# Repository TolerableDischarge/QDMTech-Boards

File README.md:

# QDMTech-Boards
A repo of all the boards designed by QuantumDarkMatter Tech.
v0.1 is very bad since I was learning as I was going for my Uni Project. There's a first time for everything I guess.
IMPORTANT: Right now the only thing under MIT license is the ZMK firmware files, the rest is a little murky. v0.2 will be MIT compatible.

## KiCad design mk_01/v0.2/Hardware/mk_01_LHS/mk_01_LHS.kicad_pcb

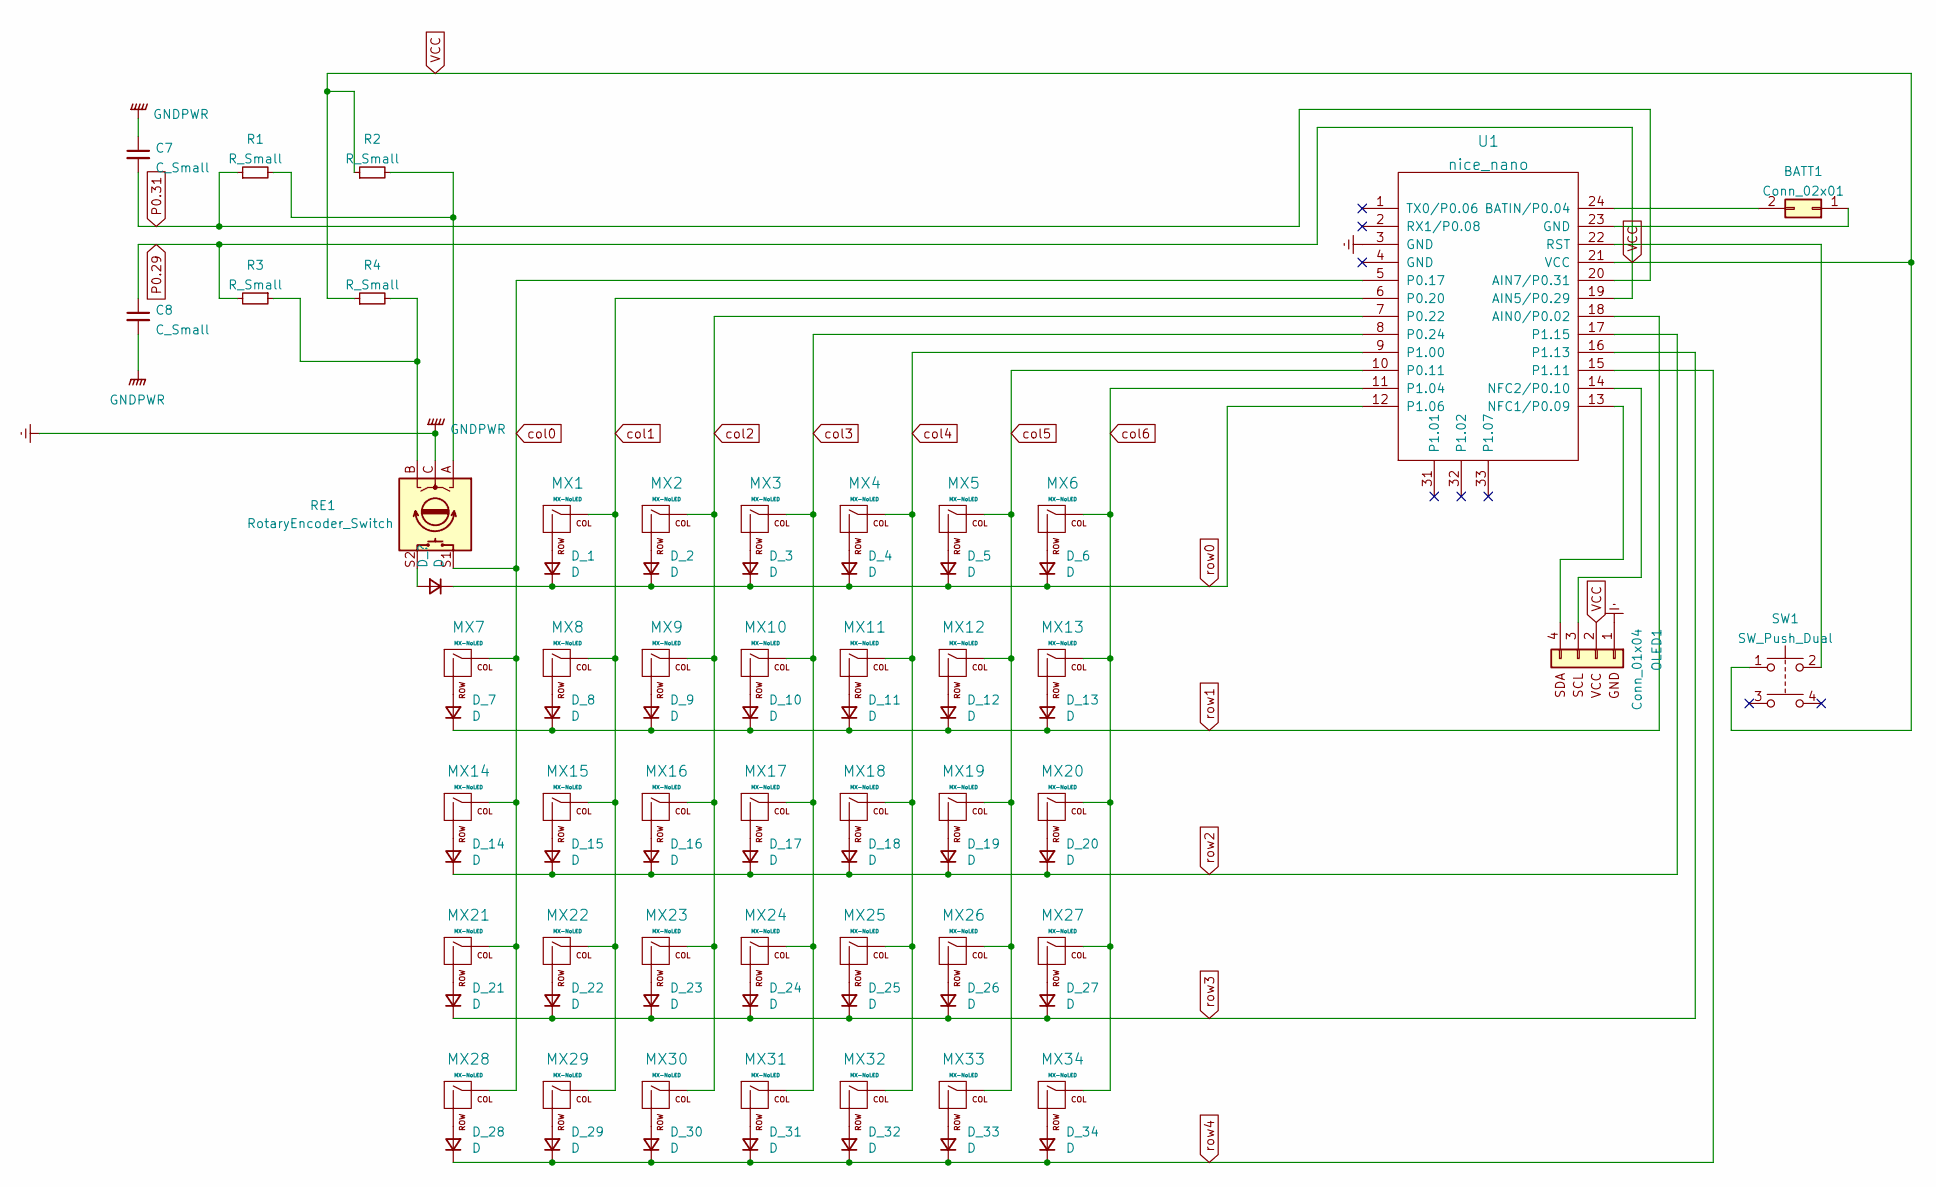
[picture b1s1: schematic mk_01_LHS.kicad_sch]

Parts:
BATT1: Conn_02x01; C_Rect_L41.5mm_W20.0mm_P37.50mm_MKS4
C7, C8: C_Small; C_0805_2012Metric_Pad1.18x1.45mm_HandSolder
D_1, D_2, D_3, D_4, D_5, D_6, D_7, D_8, D_9, D_10, D_11, D_12, D_13, D_14, D_15, D_16, D_17, D_18, D_19, D_20, D_21, D_22, D_23, D_24, D_25, D_26, D_27, D_28, D_29, D_30, D_31, D_32, D_33, D_34: D; D_SOD-123
MX1, MX2, MX3, MX4, MX5, MX6, MX7, MX8, MX9, MX10, MX11, MX12, MX13, MX14, MX15, MX16, MX17, MX18, MX19, MX20, MX21, MX22, MX23, MX24, MX25, MX26, MX27, MX28, MX29, MX30, MX31, MX32, MX33, MX34: MX-NoLED; MXOnly-1U-Hotswap-NoLED
OLED1: Conn_01x04; OLED_4Pin
R1, R2, R3, R4: R_Small; R_0805_2012Metric_Pad1.20x1.40mm_HandSolder
RE1: RotaryEncoder_Switch; RotaryEncoder_Alps_EC11E-Switch_Vertical_H20mm
SW1: SW_Push_Dual; SW_PUSH_6mm_H5mm
U1: nice_nano

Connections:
Earth: C7.1, C8.2, OLED1.1, RE1.C, U1.3 (GND), U1.4 (GND)
unnamed: BATT1.1, U1.23 (GND)
unnamed: BATT1.2, U1.24 (BATIN/P0.04)
unnamed: D_1.2 (A), MX1.2 (ROW)
unnamed: D_2.2 (A), MX2.2 (ROW)
unnamed: D_3.2 (A), MX3.2 (ROW)
unnamed: D_4.2 (A), MX4.2 (ROW)
unnamed: D_5.2 (A), MX5.2 (ROW)
unnamed: D_6.2 (A), MX6.2 (ROW)
unnamed: D_7.2 (A), MX7.2 (ROW)
unnamed: D_8.2 (A), MX8.2 (ROW)
unnamed: D_9.2 (A), MX9.2 (ROW)
unnamed: D_10.2 (A), MX10.2 (ROW)
unnamed: D_11.2 (A), MX11.2 (ROW)
unnamed: D_12.2 (A), MX12.2 (ROW)
unnamed: D_13.2 (A), MX13.2 (ROW)
unnamed: D_14.2 (A), MX14.2 (ROW)
unnamed: D_15.2 (A), MX15.2 (ROW)
unnamed: D_16.2 (A), MX16.2 (ROW)
unnamed: D_17.2 (A), MX17.2 (ROW)
unnamed: D_18.2 (A), MX18.2 (ROW)
unnamed: D_19.2 (A), MX19.2 (ROW)
unnamed: D_20.2 (A), MX20.2 (ROW)
unnamed: D_21.2 (A), MX21.2 (ROW)
unnamed: D_22.2 (A), MX22.2 (ROW)
unnamed: D_23.2 (A), MX23.2 (ROW)
unnamed: D_24.2 (A), MX24.2 (ROW)
unnamed: D_25.2 (A), MX25.2 (ROW)
unnamed: D_26.2 (A), MX26.2 (ROW)
unnamed: D_27.2 (A), MX27.2 (ROW)
unnamed: D_28.2 (A), MX28.2 (ROW)
unnamed: D_29.2 (A), MX29.2 (ROW)
unnamed: D_30.2 (A), MX30.2 (ROW)
unnamed: D_31.2 (A), MX31.2 (ROW)
unnamed: D_32.2 (A), MX32.2 (ROW)
unnamed: D_33.2 (A), MX33.2 (ROW)
unnamed: D_34.2 (A), MX34.2 (ROW)
unnamed: OLED1.3, U1.14 (NFC2/P0.10)
unnamed: OLED1.4, U1.13 (NFC1/P0.09)
unnamed: R1.2, R2.2, RE1.A
unnamed: R3.1, R4.2, RE1.B
unnamed 41: RE1.S2; also elsewhere on the board
unnamed: SW1.2, U1.22 (RST)
P0.31: C7.2, R1.1, U1.20 (AIN7/P0.31)
col0: MX7.1 (COL), MX14.1 (COL), MX21.1 (COL), MX28.1 (COL), RE1.S1, U1.5 (P0.17)
col1: MX1.1 (COL), MX8.1 (COL), MX15.1 (COL), MX22.1 (COL), MX29.1 (COL), U1.6 (P0.20)
col2: MX2.1 (COL), MX9.1 (COL), MX16.1 (COL), MX23.1 (COL), MX30.1 (COL), U1.7 (P0.22)
col3: MX3.1 (COL), MX10.1 (COL), MX17.1 (COL), MX24.1 (COL), MX31.1 (COL), U1.8 (P0.24)
col4: MX4.1 (COL), MX11.1 (COL), MX18.1 (COL), MX25.1 (COL), MX32.1 (COL), U1.9 (P1.00)
col5: MX5.1 (COL), MX12.1 (COL), MX19.1 (COL), MX26.1 (COL), MX33.1 (COL), U1.10 (P0.11)
col6: MX6.1 (COL), MX13.1 (COL), MX20.1 (COL), MX27.1 (COL), MX34.1 (COL), U1.11 (P1.04)
row0: D_1.1 (K), D_2.1 (K), D_3.1 (K), D_4.1 (K), D_5.1 (K), D_6.1 (K), U1.12 (P1.06); also elsewhere on the board
row1: D_7.1 (K), D_8.1 (K), D_9.1 (K), D_10.1 (K), D_11.1 (K), D_12.1 (K), D_13.1 (K), U1.18 (AIN0/P0.02)
row2: D_14.1 (K), D_15.1 (K), D_16.1 (K), D_17.1 (K), D_18.1 (K), D_19.1 (K), D_20.1 (K), U1.17 (P1.15)
row3: D_21.1 (K), D_22.1 (K), D_23.1 (K), D_24.1 (K), D_25.1 (K), D_26.1 (K), D_27.1 (K), U1.16 (P1.13)
row4: D_28.1 (K), D_29.1 (K), D_30.1 (K), D_31.1 (K), D_32.1 (K), D_33.1 (K), D_34.1 (K), U1.15 (P1.11)

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
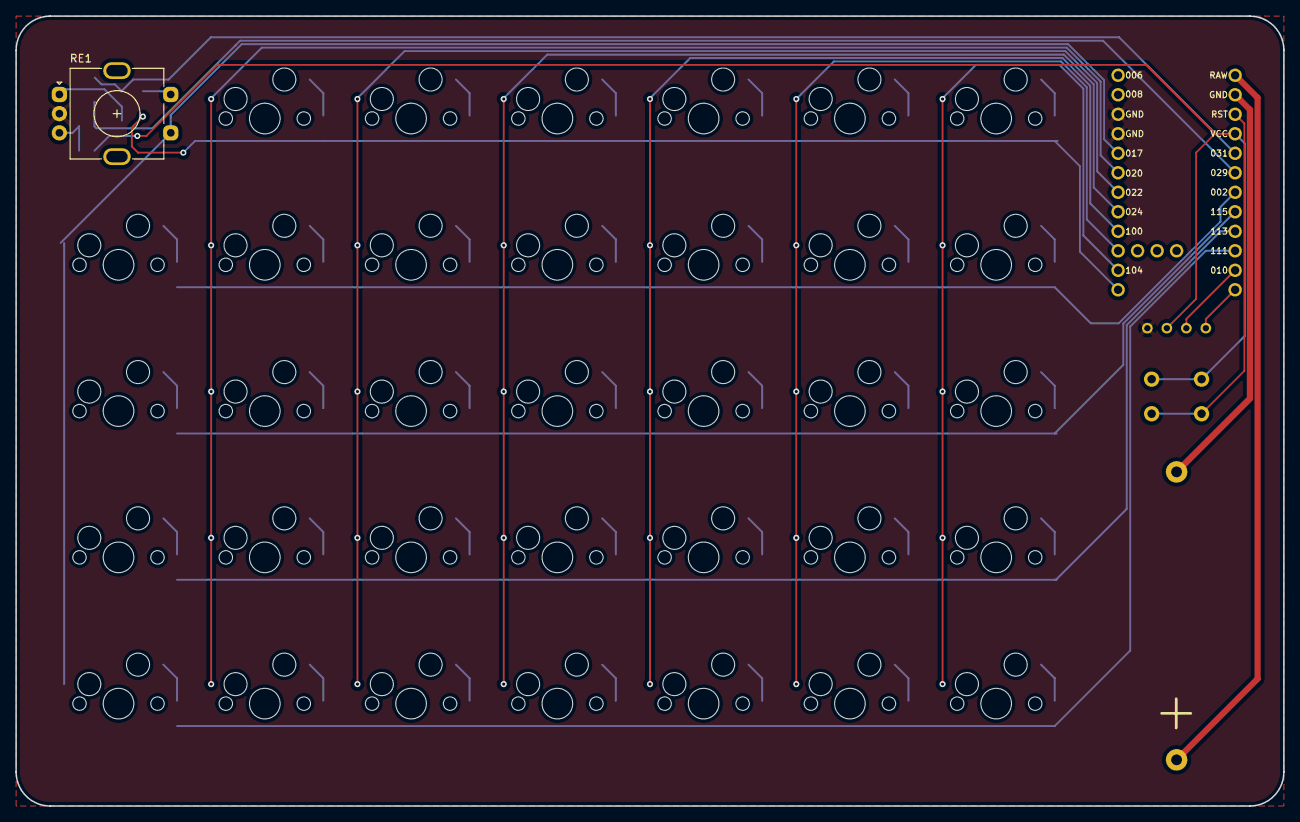
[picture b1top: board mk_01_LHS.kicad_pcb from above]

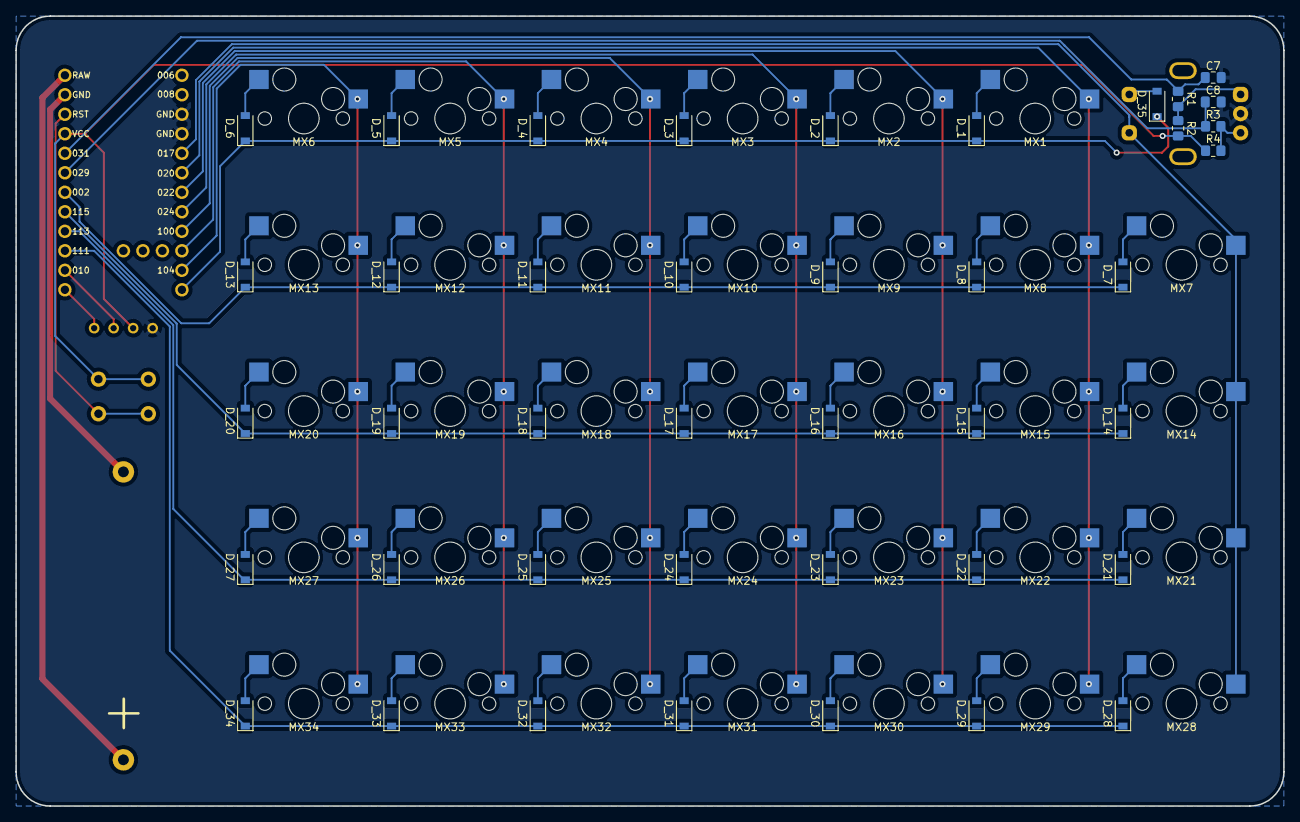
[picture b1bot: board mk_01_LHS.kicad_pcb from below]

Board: 2 copper layers, 165.1 x 102.9 mm, 80 parts (41 on the bottom side), 58 nets.

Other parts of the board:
D_35: D; D_SOD-123

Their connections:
unnamed 41: D_35.2 (A); also elsewhere on the board
row0: D_35.1 (K); also elsewhere on the board

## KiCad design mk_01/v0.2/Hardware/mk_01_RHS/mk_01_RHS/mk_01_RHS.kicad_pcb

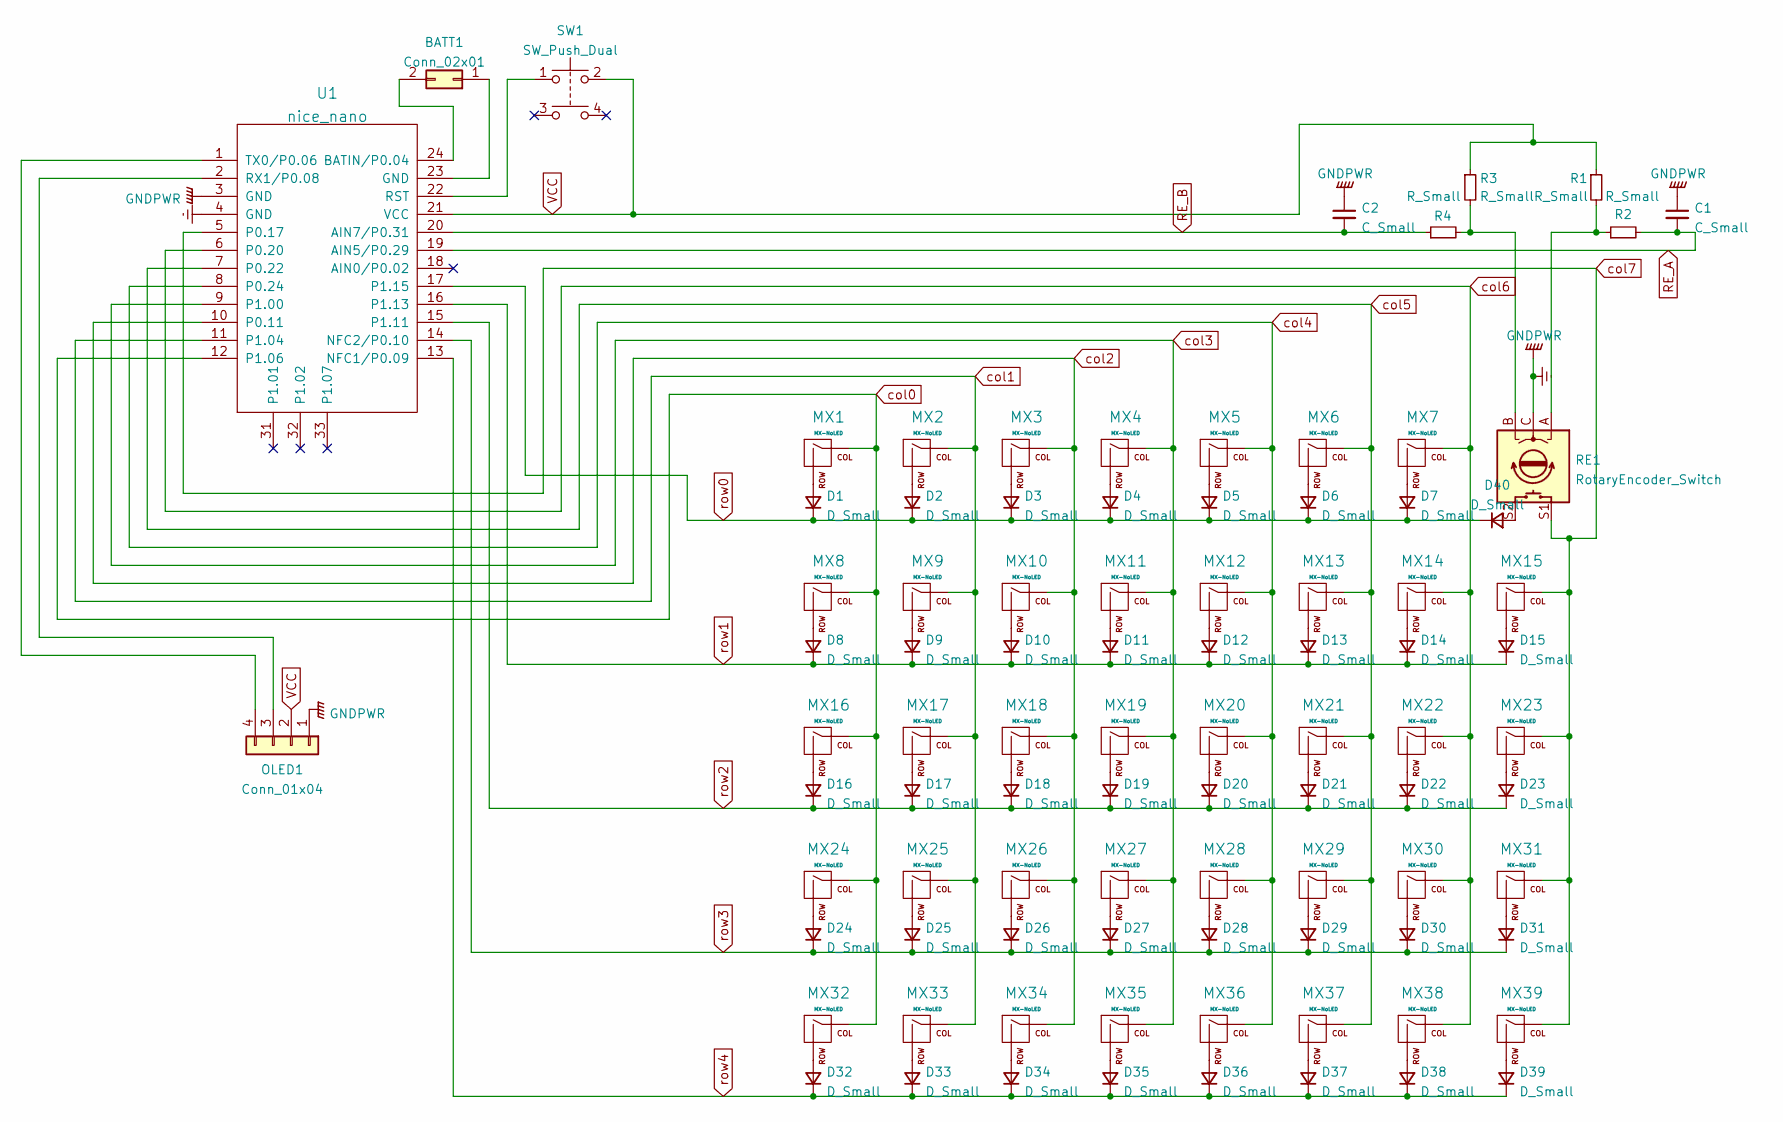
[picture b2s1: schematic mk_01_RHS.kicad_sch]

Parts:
BATT1: Conn_02x01; C_Rect_L41.5mm_W20.0mm_P37.50mm_MKS4
C1, C2: C_Small; C_0805_2012Metric_Pad1.18x1.45mm_HandSolder
D1, D2, D3, D4, D5, D6, D7, D8, D9, D10, D11, D12, D13, D14, D15, D16, D17, D18, D19, D20, D21, D22, D23, D24, D25, D26, D27, D28, D29, D30, D31, D32, D33, D34, D35, D36, D37, D38, D39, D40: D_Small; D_SOD-123
MX1, MX2, MX3, MX4, MX5, MX6, MX7, MX8, MX9, MX10, MX11, MX12, MX13, MX14, MX15, MX16, MX17, MX18, MX19, MX20, MX21, MX22, MX23, MX24, MX25, MX26, MX27, MX28, MX29, MX30, MX31, MX32, MX33, MX34, MX35, MX36, MX37, MX38, MX39: MX-NoLED; MXOnly-1U-Hotswap-NoLED
OLED1: Conn_01x04; OLED_4Pin
R1, R2, R3, R4: R_Small; R_0805_2012Metric_Pad1.20x1.40mm_HandSolder
RE1: RotaryEncoder_Switch; RotaryEncoder_Alps_EC11E-Switch_Vertical_H20mm
SW1: SW_Push_Dual; SW_PUSH_6mm_H5mm
U1: nice_nano

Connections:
Earth: C1.1, C2.1, OLED1.1, RE1.C, U1.3 (GND), U1.4 (GND)
unnamed: BATT1.1, U1.23 (GND)
unnamed: BATT1.2, U1.24 (BATIN/P0.04)
unnamed: D1.2 (A), MX1.2 (ROW)
unnamed: D2.2 (A), MX2.2 (ROW)
unnamed: D3.2 (A), MX3.2 (ROW)
unnamed: D4.2 (A), MX4.2 (ROW)
unnamed: D5.2 (A), MX5.2 (ROW)
unnamed: D6.2 (A), MX6.2 (ROW)
unnamed: D7.2 (A), MX7.2 (ROW)
unnamed: D8.2 (A), MX8.2 (ROW)
unnamed: D9.2 (A), MX9.2 (ROW)
unnamed: D10.2 (A), MX10.2 (ROW)
unnamed: D11.2 (A), MX11.2 (ROW)
unnamed: D12.2 (A), MX12.2 (ROW)
unnamed: D13.2 (A), MX13.2 (ROW)
unnamed: D14.2 (A), MX14.2 (ROW)
unnamed: D15.2 (A), MX15.2 (ROW)
unnamed: D16.2 (A), MX16.2 (ROW)
unnamed: D17.2 (A), MX17.2 (ROW)
unnamed: D18.2 (A), MX18.2 (ROW)
unnamed: D19.2 (A), MX19.2 (ROW)
unnamed: D20.2 (A), MX20.2 (ROW)
unnamed: D21.2 (A), MX21.2 (ROW)
unnamed: D22.2 (A), MX22.2 (ROW)
unnamed: D23.2 (A), MX23.2 (ROW)
unnamed: D24.2 (A), MX24.2 (ROW)
unnamed: D25.2 (A), MX25.2 (ROW)
unnamed: D26.2 (A), MX26.2 (ROW)
unnamed: D27.2 (A), MX27.2 (ROW)
unnamed: D28.2 (A), MX28.2 (ROW)
unnamed: D29.2 (A), MX29.2 (ROW)
unnamed: D30.2 (A), MX30.2 (ROW)
unnamed: D31.2 (A), MX31.2 (ROW)
unnamed: D32.2 (A), MX32.2 (ROW)
unnamed: D33.2 (A), MX33.2 (ROW)
unnamed: D34.2 (A), MX34.2 (ROW)
unnamed: D35.2 (A), MX35.2 (ROW)
unnamed: D36.2 (A), MX36.2 (ROW)
unnamed: D37.2 (A), MX37.2 (ROW)
unnamed: D38.2 (A), MX38.2 (ROW)
unnamed: D39.2 (A), MX39.2 (ROW)
unnamed: D40.2 (A), RE1.S2
unnamed: R3.2, R4.2, RE1.B
unnamed: R1.2, R2.1, RE1.A
unnamed: SW1.1, U1.22 (RST)
unnamed: OLED1.4, U1.1 (TX0/P0.06)
unnamed: OLED1.3, U1.2 (RX1/P0.08)
RE_A: C1.2, R2.2, U1.19 (AIN5/P0.29)
RE_B: C2.2, R4.1, U1.20 (AIN7/P0.31)
VCC: OLED1.2, R1.1, R3.1, SW1.2, U1.21 (VCC)
col0: MX1.1 (COL), MX8.1 (COL), MX16.1 (COL), MX24.1 (COL), MX32.1 (COL), U1.12 (P1.06)
col1: MX2.1 (COL), MX9.1 (COL), MX17.1 (COL), MX25.1 (COL), MX33.1 (COL), U1.11 (P1.04)
col2: MX3.1 (COL), MX10.1 (COL), MX18.1 (COL), MX26.1 (COL), MX34.1 (COL), U1.10 (P0.11)
col3: MX4.1 (COL), MX11.1 (COL), MX19.1 (COL), MX27.1 (COL), MX35.1 (COL), U1.9 (P1.00)
col4: MX5.1 (COL), MX12.1 (COL), MX20.1 (COL), MX28.1 (COL), MX36.1 (COL), U1.8 (P0.24)
col5: MX6.1 (COL), MX13.1 (COL), MX21.1 (COL), MX29.1 (COL), MX37.1 (COL), U1.7 (P0.22)
col6: MX7.1 (COL), MX14.1 (COL), MX22.1 (COL), MX30.1 (COL), MX38.1 (COL), U1.6 (P0.20)
col7: MX15.1 (COL), MX23.1 (COL), MX31.1 (COL), MX39.1 (COL), RE1.S1, U1.5 (P0.17)
row0: D1.1 (K), D2.1 (K), D3.1 (K), D4.1 (K), D5.1 (K), D6.1 (K), D7.1 (K), D40.1 (K), U1.17 (P1.15)
row1: D8.1 (K), D9.1 (K), D10.1 (K), D11.1 (K), D12.1 (K), D13.1 (K), D14.1 (K), D15.1 (K), U1.16 (P1.13)
row2: D16.1 (K), D17.1 (K), D18.1 (K), D19.1 (K), D20.1 (K), D21.1 (K), D22.1 (K), D23.1 (K), U1.15 (P1.11)
row3: D24.1 (K), D25.1 (K), D26.1 (K), D27.1 (K), D28.1 (K), D29.1 (K), D30.1 (K), D31.1 (K), U1.14 (NFC2/P0.10)
row4: D32.1 (K), D33.1 (K), D34.1 (K), D35.1 (K), D36.1 (K), D37.1 (K), D38.1 (K), D39.1 (K), U1.13 (NFC1/P0.09)

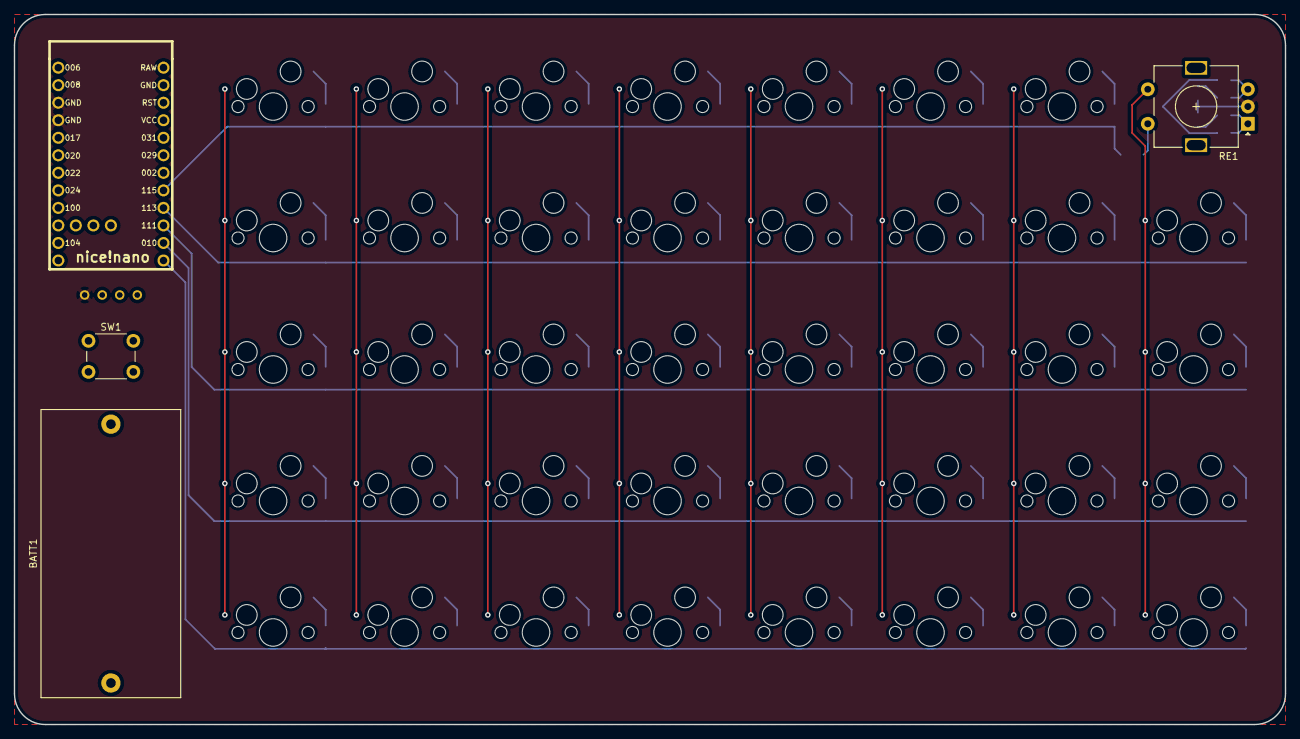
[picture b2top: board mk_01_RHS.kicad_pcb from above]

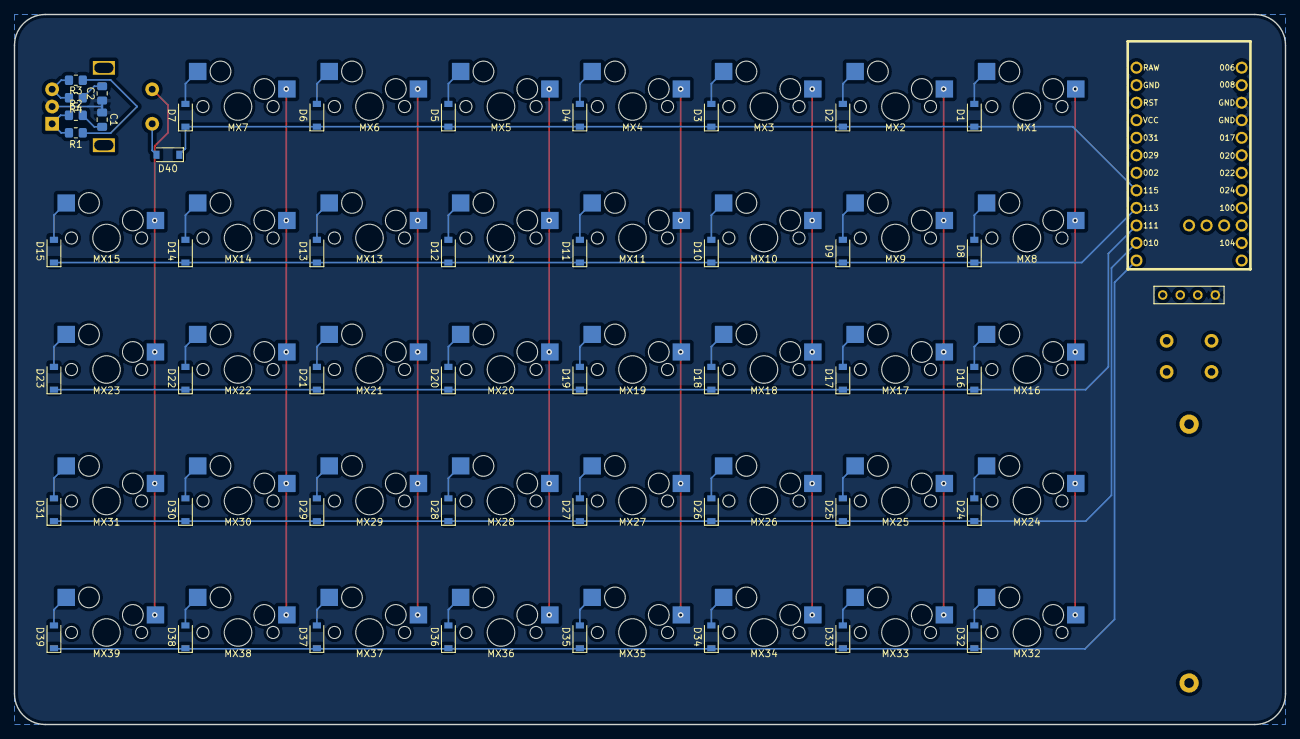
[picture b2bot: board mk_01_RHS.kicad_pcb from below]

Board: 2 copper layers, 184.1 x 102.9 mm, 90 parts (46 on the bottom side), 64 nets.

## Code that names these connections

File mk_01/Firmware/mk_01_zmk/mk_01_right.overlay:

#include "mk_01.dtsi" // Notice that the main dtsi files are included in the overlay.

&kscan0 {
    col-gpios
        = <&pro_micro * GPIO_ACTIVE_HIGH> // col0 in the schematic
        , <&pro_micro * GPIO_ACTIVE_HIGH> // col1 in the schematic
        , <&pro_micro * GPIO_ACTIVE_HIGH> // col2 in the schematic
        , <&pro_micro 9 GPIO_ACTIVE_HIGH> // col3 in the schematic
        , <&pro_micro 5 GPIO_ACTIVE_HIGH> // col4 in the schematic
        , <&pro_micro 6 GPIO_ACTIVE_HIGH> // col5 in the schematic
        , <&pro_micro 7 GPIO_ACTIVE_HIGH> // col6 in the schematic
        , <&pro_micro 8 GPIO_ACTIVE_HIGH> // col7 in the schematic
        ;
};

&left_encoder {
    status = "okay";
};

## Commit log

2022-05-03 First ZMK config
    Here's a first attempt at the config for ZMK
2022-05-05 Reorganising the file structure
2022-05-05 Uploading the hardware
    Since I discovered version control very late in the development process, these files are very very messy and badly organised. Next version will be much better learning from the mistakes I made.
2022-05-13 Updates
    Incldues updates to ZMK and the creation of the BlueMicro firmware folder
2022-05-13 Update README.md
    Fixing grammar and clearing up confusing language
2022-07-12 v0.2 Started plus housekeeping
    I've started redesigning v0.1 into something better with v0.2. This time I'm going to ignore RGB lighting with the goal of completing a working product first, then adding extra features in the future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
2022-07-13 Hardware updates
    Keyboard matrix is complete, on both the schematic and the board design. To keep the design simple, I will remove the LEDs.
2022-07-13 LED removal and progress
    The LEDs have been removed from the schematic and the board design, edge cuts and routing for the key matrix have been added, as has the capacitor|resistor layout for the rotary encoder (which I may 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
2022-07-13 Updated PCB design
    The PCB design has been updated and is now relatively complete. The hardware is fully MIT compliant, as all libraries used are under MIT license, and the design is entirely my own. Now it's time to r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
2022-07-13 Updated schematic
    Updated schematic that was meant to be included in the last commit.
2022-07-14 PCB completed and rounded
    The PCB is pretty much complete for the left hand side, and I've generated a seperate file with rounded tracks using the round tracks plugin.
2022-07-14 Finalising layout and troubleshooting round-tracks
    The layout is pretty much complete, with all necessary components wired correctly. round-tracks keeps refusing to round one of the traces. A label free version has been added, however I'll probably r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
2022-07-15 Left Hand Side completion and housekeeping
    The left hand side has been completed, time to start on the right hand side. I've cleared out the right hand side files, because this time I'm going to start from scratch.
2022-07-15 Starting the right hand side
    The right hand side schematic has been completed, subject to change based on the board design. The board design has also already been started.
2022-07-16 Right hand side mostly completed
    The right hand side of the keyboard is pretty much complete, and after a final checkover of everything I think it's ready for production. I'm going to clean up the left hand side board design and sch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
